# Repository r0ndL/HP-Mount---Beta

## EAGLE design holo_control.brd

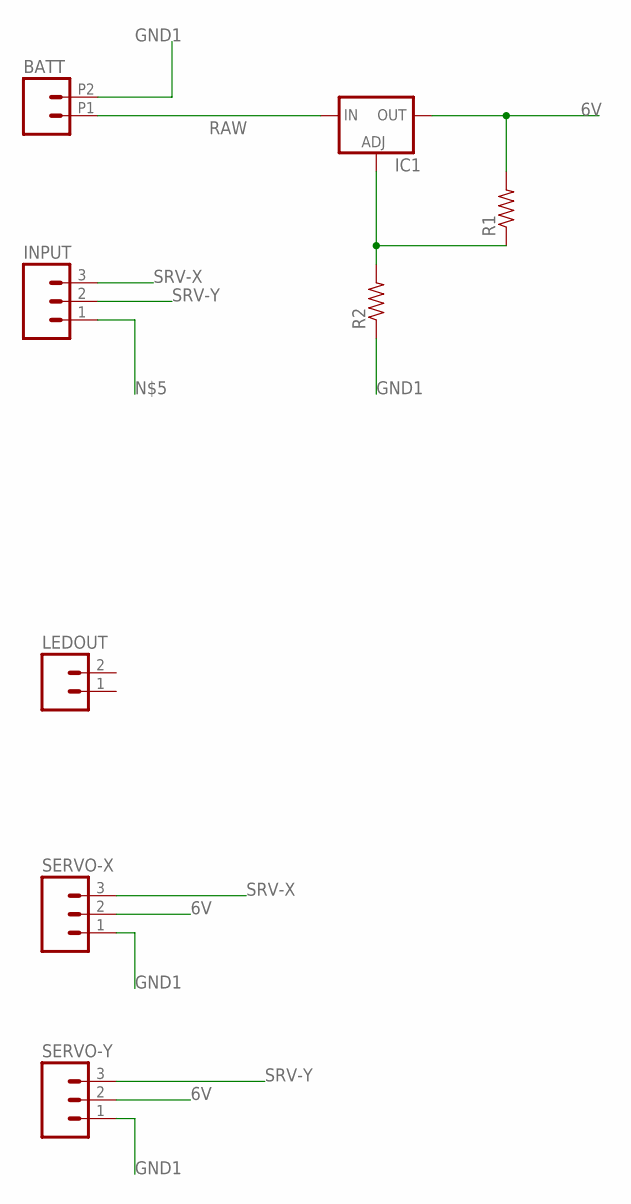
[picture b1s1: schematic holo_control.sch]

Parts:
BATT: M022.54MM_SCREWTERM; 1X02_2.54_SCREWTERM
IC1: LM317TS; 317TS
INPUT: M03PTH; 1X03
LEDOUT: M02PTH; 1X02
R1, R2: RESISTORPTH-1/4W; AXIAL-0.4
SERVO-X: M03PTH; 1X03
SERVO-Y: M03PTH; 1X03

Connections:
6V: IC1.2 (OUT), R1.P$2 (2), SERVO-X.2, SERVO-Y.2
GND1: BATT.P2 (2), R2.P$1 (1), SERVO-X.1, SERVO-Y.1
unnamed: IC1.1 (ADJ), R1.P$1 (1), R2.P$2 (2)
RAW: BATT.P1 (1), IC1.3 (IN)
SRV-X: INPUT.3, SERVO-X.3
SRV-Y: INPUT.2, SERVO-Y.3

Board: 2 copper layers, 8 parts (0 on the bottom side), 6 nets, no tracks yet.

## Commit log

2016-03-03 :circus_tent: Added .gitattributes & .gitignore files
2016-03-03 initial upload

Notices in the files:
parts and their libraries:
SparkFun-Connectors: Licensing: Creative Commons ShareAlike 4.0 International - https://creativecommons.org/licenses/by-sa/4.0
